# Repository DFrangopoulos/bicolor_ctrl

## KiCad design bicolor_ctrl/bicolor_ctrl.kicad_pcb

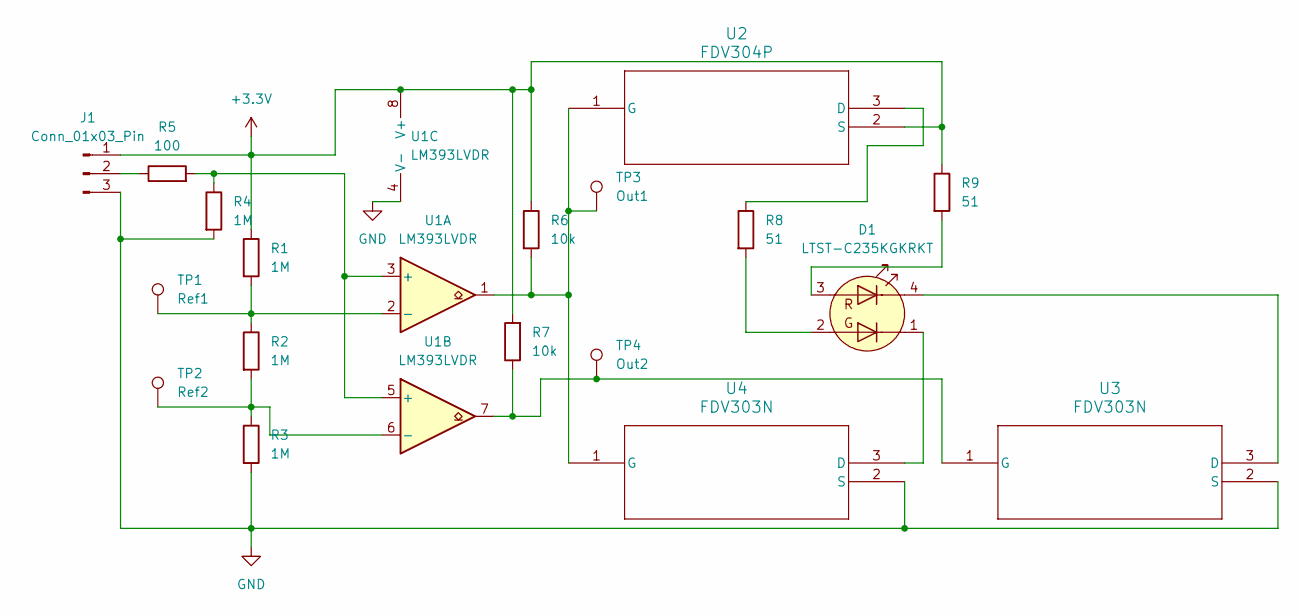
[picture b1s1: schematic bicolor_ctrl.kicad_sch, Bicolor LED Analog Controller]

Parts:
D1: LTST-C235KGKRKT; LED_LiteOn_LTST-C235KGKRKT
J1: Conn_01x03_Pin; PinHeader_1x03_P2.54mm_Vertical
R1, R2, R3, R4: 1M; R_0805_2012Metric_Pad1.20x1.40mm_HandSolder
R5: 100; R_0805_2012Metric_Pad1.20x1.40mm_HandSolder
R6, R7: 10k; R_0805_2012Metric_Pad1.20x1.40mm_HandSolder
R8, R9: 51; R_1206_3216Metric_Pad1.30x1.75mm_HandSolder
TP1: Ref1; TestPoint_Pad_1.0x1.0mm
TP2: Ref2; TestPoint_Pad_1.0x1.0mm
TP3: Out1; TestPoint_Pad_1.0x1.0mm
TP4: Out2; TestPoint_Pad_1.0x1.0mm
U1: LM393LVDR; SOIC-8_3.9x4.9mm_P1.27mm
U2: FDV304P; SOT-23-3L_FAS-M
U3, U4: FDV303N; SOT-23-3L_FAS-M

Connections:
+3.3V: J1.1, R1.1, R6.1, R7.2, R9.1, U1.8 (V+), U2.2 (S)
GND: J1.3, R3.2, R4.2, U1.4 (V-), U3.2 (S), U4.2 (S)
unnamed: D1.3 (A1), R9.2
unnamed: D1.2 (A2), R8.2
unnamed: D1.4 (K1), U3.3 (D)
unnamed: D1.1 (K2), U4.3 (D)
unnamed: J1.2, R5.1
unnamed: R4.1, R5.2, U1.3 (+), U1.5 (+)
unnamed: R1.2, R2.1, TP1.1, U1.2 (-)
unnamed: R2.2, R3.1, TP2.1, U1.6 (-)
unnamed: R8.1, U2.3 (D)
unnamed: R6.2, TP3.1, U1.1, U2.1 (G), U4.1 (G)
unnamed: R7.1, TP4.1, U1.7, U3.1 (G)

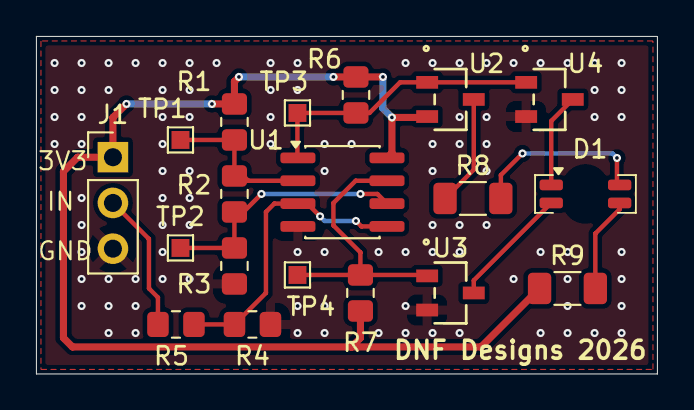
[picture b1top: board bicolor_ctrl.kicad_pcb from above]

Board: 2 copper layers, 34.5 x 18.8 mm, 19 parts (0 on the bottom side), 13 nets.

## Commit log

2026-05-10 Full design
2026-05-10 Added branding
